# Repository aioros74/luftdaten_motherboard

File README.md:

# Luftdaten motherboard
## Description
### French version
La carte support luftdaten v1r1 est un circuit imprimé destiné à simplifier et apporter plus d’options au montage du détecteur de particules fines du projet Sensor Community (https://sensor.community/fr/). La page du montage: https://sensor.community/fr/sensors/airrohr/

Cette carte permet :
* D’exposer les IOs de l’ESP8266 sur des connecteurs.
* De fixer l’ESP8266 et les détecteurs de particules fines SDS011 et PMS7003 sur une même carte, et évite les câblages volants.
* D’utiliser le câble fourni avec le SDS011.
* Différentes options d’alimentation :
  * Câble USB.
  * Alimentation externe directe.
  * Alimentation externe avec régulateurs DC/DC.

### English version

The luftdaten v1r1 motherboard is a printed circuit intended to simplify and provide more options for mounting the particule matter sensors of the Sensor Community project (https://sensor.community/en/). Link to the hardware: https://sensor.community/fr/sensors/airrohr/

This card allows:
* Access to ESP8266 I/0
* To fix the ESP8266 and the particule matter sensors SDS011 and PMS7003 on the same card, and avoid flying cables.
* Use the cable provided with the SDS011.
* Several power supply options:
	* USB cable.
	* External direct power supply.
	* External power supply with DC/DC regulators.

## Documentation
* Documentation de la carte: [documentation](./doc/Carte%20Support%20Luftdaten%20v1r1.pdf)
* Schéma de la carte: [schéma](./doc/schematic_uftdaten_v1r1.pdf)
* CAO Eagle: [CAO](./cao/)
* Fichiers de fabrication: [gerbers](./manufacturing/)
* Photos du PCB

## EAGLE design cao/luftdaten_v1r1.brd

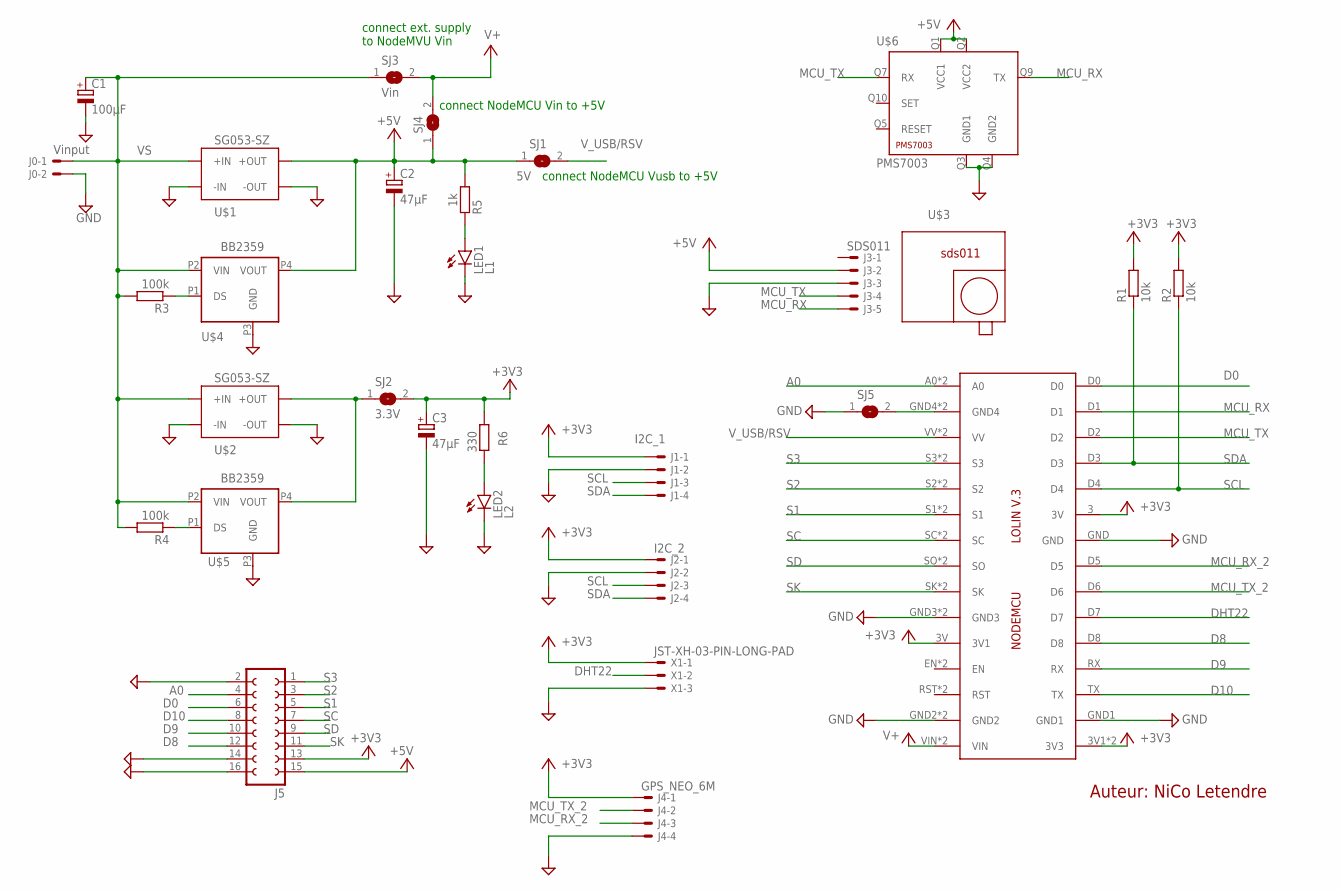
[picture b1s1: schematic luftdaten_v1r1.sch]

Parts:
C1: 100µF; E3,5-8
C2, C3: 47µF; E2,5-5
IC2: NodeMCU; LOLINV3
J0: Vinput; JST-XH-02-PACKAGE-LONG-PAD
J1: I2C_1; JST-XH-04-PACKAGE-LONG-PAD
J2: I2C_2; JST-XH-04-PACKAGE-LONG-PAD
J3: SDS011; JST-XH-05-PACKAGE-LONG-PAD
J4: GPS_NEO_6M; JST-XH-04-PACKAGE-LONG-PAD
J5: FE08-2
LED1: L1; CHIPLED_0805
LED2: L2; CHIPLED_0805
R1, R2: 10k; R0805
R3, R4: 100k; R0805
R5: 1k; R0805
R6: 330; R0805
SJ1: 5V; SJ
SJ2: 3.3V; SJ
SJ3: Vin; SJ
SJ4, SJ5: SJ
U$1, U$2: SG053-SZ
U$3: SDSO11; SDS011
U$4, U$5: BB2359
U$6: PMS7003
X1: JST-XH-03-PIN-LONG-PAD; JST-XH-03-PACKAGE-LONG-PAD

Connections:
+3V3: C3.+, IC2.3 (3V), IC2.3V (3V1), IC2.3V1 (3V3), IC2.3V3, J1.1, J2.1, J4.1, J5.13, R1.2, R2.2, R6.1, SJ2.2, X1.1
+5V: C2.+, J3.2, J5.15, R5.1, SJ1.1, SJ4.1, U$1.P$5 (+OUT), U$1.P$6 (+OUT), U$4.P4 (VOUT), U$6.Q1 (VCC1), U$6.Q2 (VCC2)
A0: IC2.A0, IC2.A1 (A0), J5.4
D0: IC2.D0, J5.6
D8: IC2.D8, J5.12
D9: IC2.RX, J5.10
D10: IC2.TX, J5.8
DHT22: IC2.D7, X1.2
GND: C1.-, C2.-, C3.-, IC2.GND, IC2.GND1, IC2.GND2, IC2.GND3, IC2.GND5 (GND2), IC2.GND6 (GND3), J0.2, J1.2, J2.2, J3.3, J4.4, J5.2, J5.14, J5.16, LED1.C, LED2.C, SJ5.1, U$1.P$1 (-IN), U$1.P$2 (-IN), U$1.P$7 (-OUT), U$1.P$8 (-OUT), U$2.P$1 (-IN), U$2.P$2 (-IN), U$2.P$7 (-OUT), U$2.P$8 (-OUT), U$4.P3 (GND), U$5.P3 (GND), U$6.Q3 (GND1), U$6.Q4 (GND2), X1.3
MCU_RX: IC2.D1, J3.5, U$6.Q9 (TX)
MCU_RX_2: IC2.D5, J4.3
MCU_TX: IC2.D2, J3.4, U$6.Q7 (RX)
MCU_TX_2: IC2.D6, J4.2
unnamed: IC2.GND4, IC2.GND7 (GND4), SJ5.2
unnamed: SJ2.1, U$2.P$5 (+OUT), U$2.P$6 (+OUT), U$5.P4 (VOUT)
unnamed: R3.1, U$4.P1 (DS)
unnamed: R4.1, U$5.P1 (DS)
unnamed: LED1.A, R5.2
unnamed: LED2.A, R6.2
S1: IC2.S1, IC2.S4 (S1), J5.5
S2: IC2.S2, IC2.S5 (S2), J5.3
S3: IC2.S3, IC2.S6 (S3), J5.1
SC: IC2.SC, IC2.SC1 (SC), J5.7
SCL: IC2.D4, J1.3, J2.3, R2.1
SD: IC2.SO, IC2.SO1 (SO), J5.9
SDA: IC2.D3, J1.4, J2.4, R1.1
SK: IC2.SK, IC2.SK1 (SK), J5.11
V+: IC2.VIN, IC2.VIN1 (VIN), SJ3.2, SJ4.2
VS: C1.+, J0.1, R3.2, R4.2, SJ3.1, U$1.P$3 (+IN), U$1.P$4 (+IN), U$2.P$3 (+IN), U$2.P$4 (+IN), U$4.P2 (VIN), U$5.P2 (VIN)
V_USB/RSV: IC2.VV, IC2.VV1 (VV), SJ1.2

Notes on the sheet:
connect NodeMCU Vusb to +5V
connect ext. supply to NodeMVU Vin
connect NodeMCU Vin to +5V
Auteur: NiCo Letendre

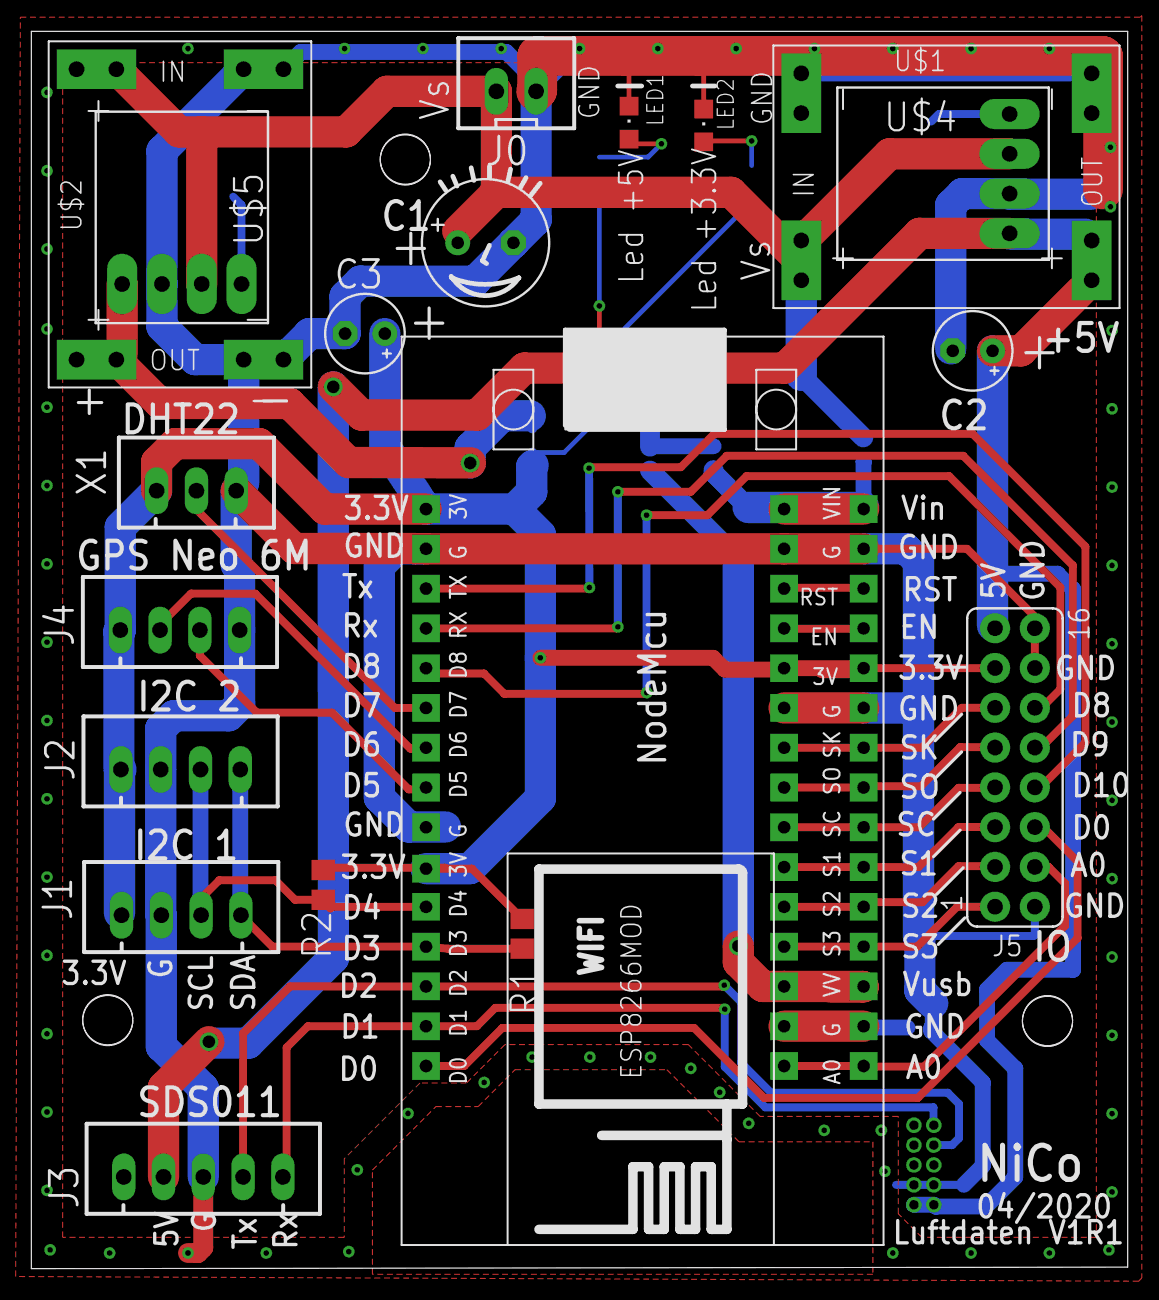
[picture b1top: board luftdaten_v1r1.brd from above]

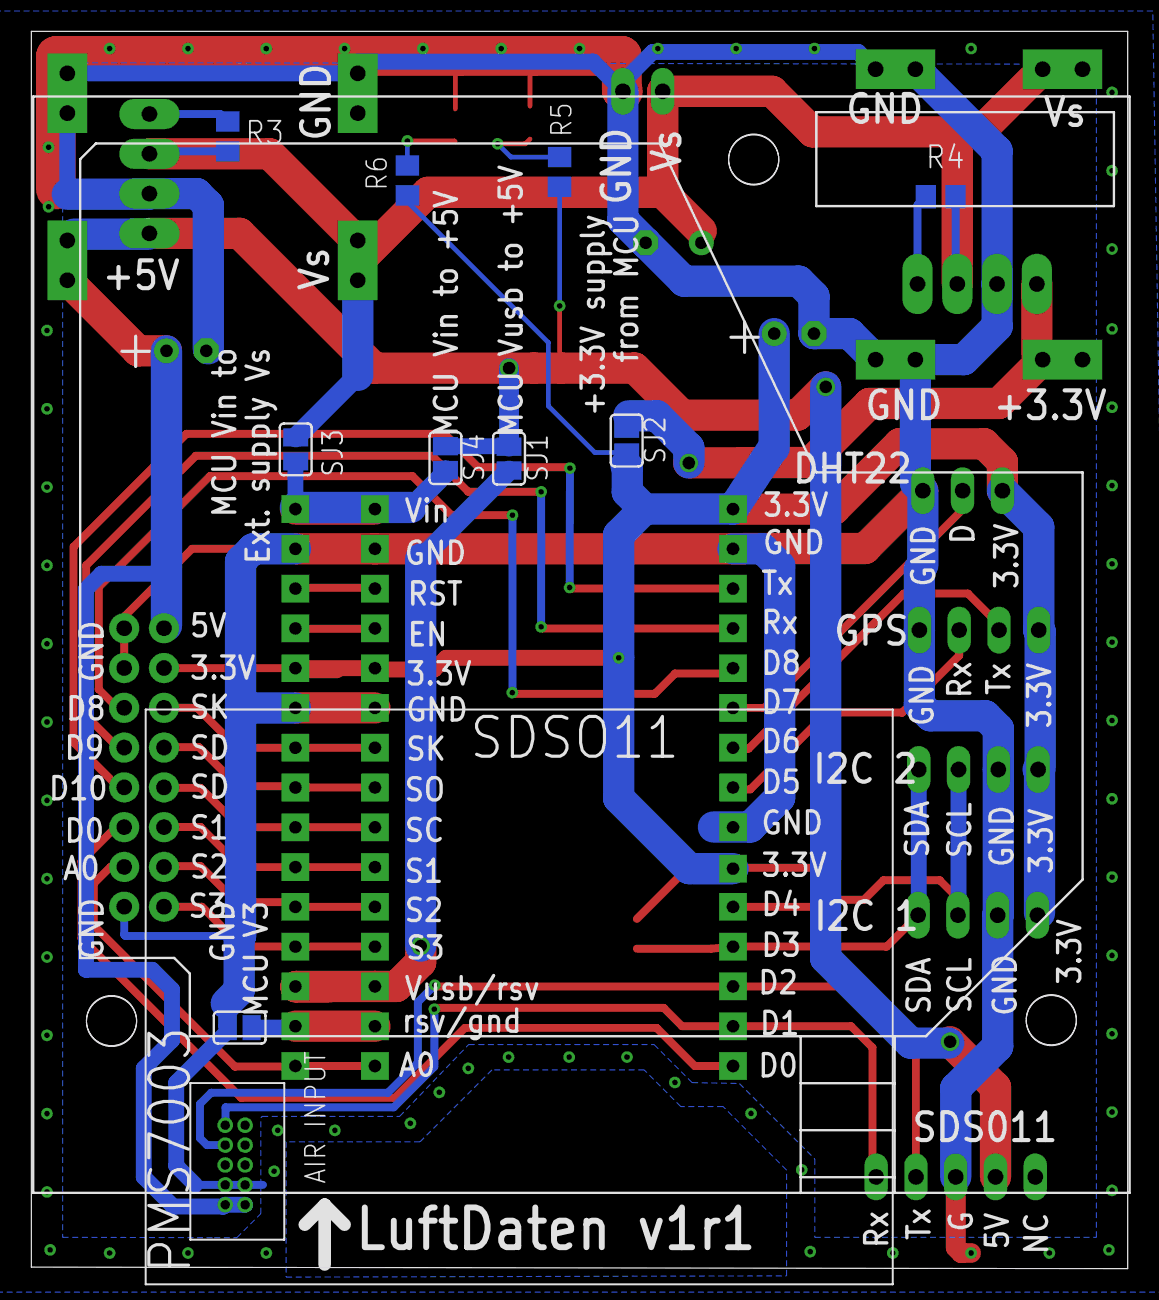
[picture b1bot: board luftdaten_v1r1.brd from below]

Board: 2 copper layers, 69.9 x 78.9 mm, 30 parts (11 on the bottom side), 30 nets.

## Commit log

2020-04-27 Init
2020-04-27 Add more info in README.md, and photos in ./doc
2020-04-28 Correction in "Carte Support Luftdaten v1r1.pdf"
2020-04-28 update sensor image
2020-05-01 English version of README.md
2021-10-12 Update README.md
    Change Luftdaten references to Sensor Community
